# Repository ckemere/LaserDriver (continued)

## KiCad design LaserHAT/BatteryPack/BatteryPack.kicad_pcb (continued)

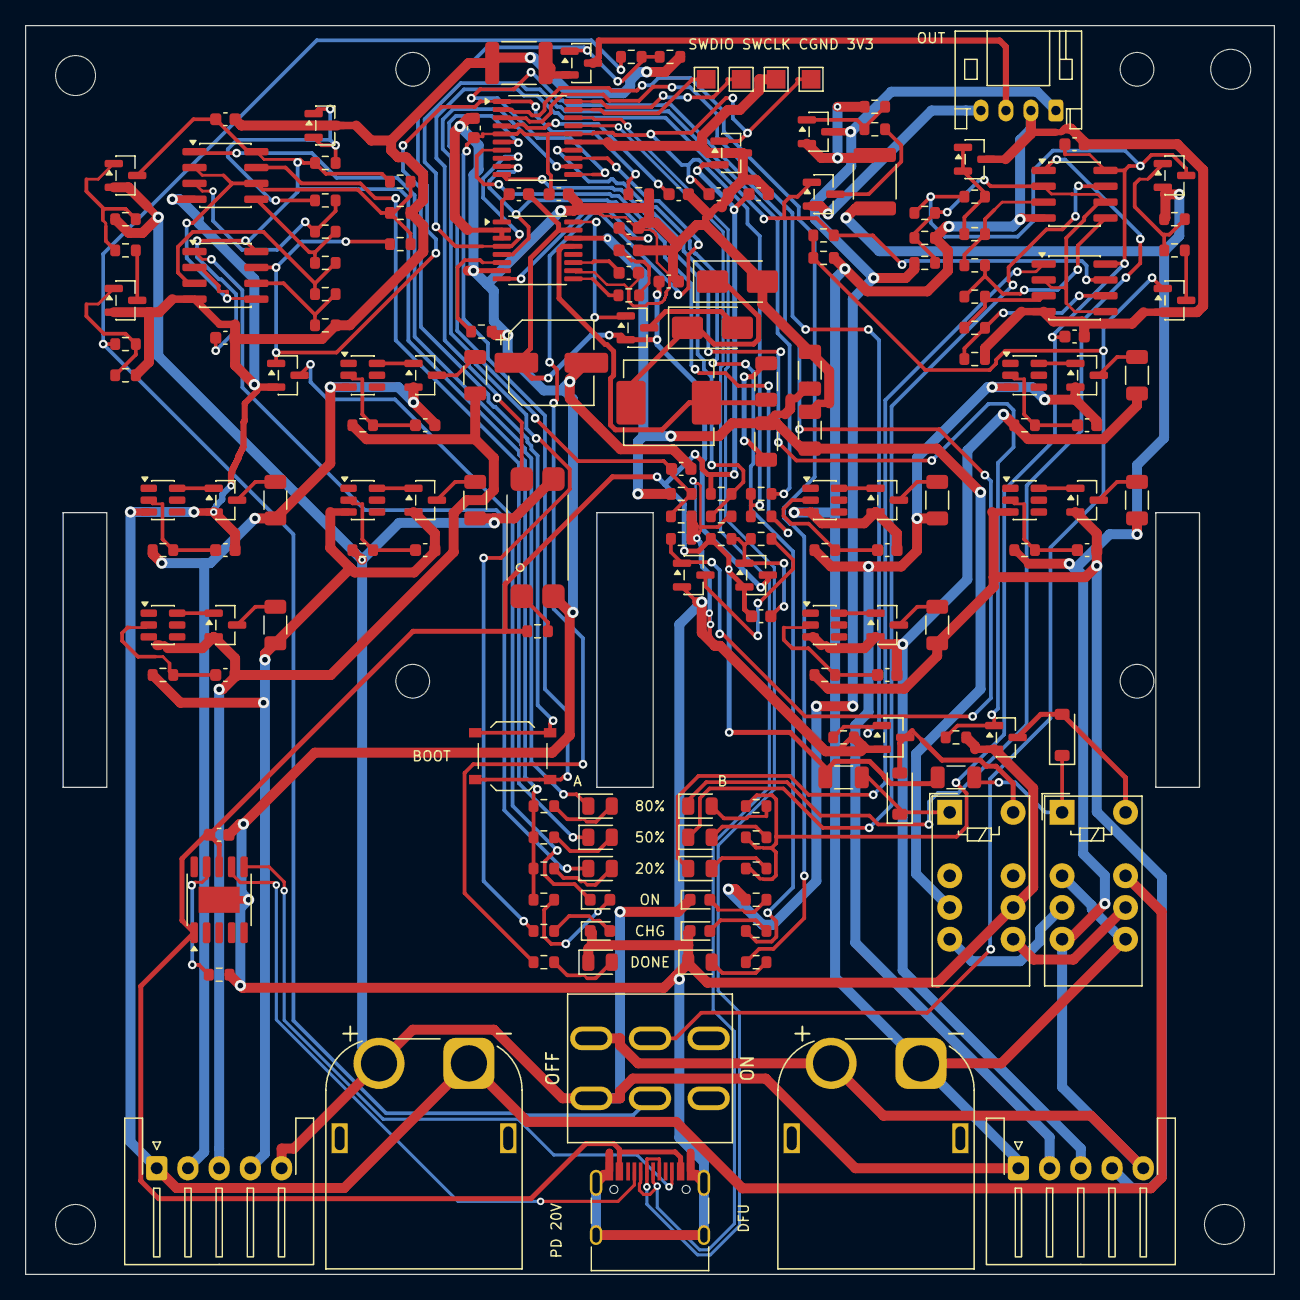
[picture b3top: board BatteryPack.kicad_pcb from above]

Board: 2 copper layers, 100.0 x 100.0 mm, 187 parts (0 on the bottom side), 127 nets.

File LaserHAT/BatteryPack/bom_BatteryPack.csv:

Ref,Value,Footprint,LCSC,Note
J5,S5B-XH-A-1(LF)(SN),JST_XH_S5B-XH-A-1_1x05_P2.50mm_Horizontal,C163038,
J6,S5B-XH-A-1(LF)(SN),JST_XH_S5B-XH-A-1_1x05_P2.50mm_Horizontal,C163038,
J7,XT60PW-M,XT60PW-M,C98732,
J8,XT60PW-M,XT60PW-M,C98732,
SW1,CAX-MTS202B2-BB-20.5JL,SW_MTS-202,C55159891,
R82,1M,R_0603_1608Metric,C22935,
F1,MF-MSMF010-2,Fuse_1812_4532Metric,C12430,
Q1,AO3401A,SOT-23,C15127,
R1,100k,R_0603_1608Metric,C25803,
R2,100k,R_0603_1608Metric,C25803,
Q22,2N7002,SOT-23,C8545,
R81,1M,R_0603_1608Metric,C22935,
U15,LM393DR2G,SOIC-8_3.9x4.9mm_P1.27mm,C7955,
D11,KT-0603R,LED_0603_1608Metric,C2286,
R54,13k,R_0603_1608Metric,C22797,
F2,MF-MSMF010-2,Fuse_1812_4532Metric,C12430,
Q11,AO3400A,SOT-23,C20917,
R39,100k,R_0603_1608Metric,C25803,
R40,100k,R_0603_1608Metric,C25803,
U2,LM393DR2G,SOIC-8_3.9x4.9mm_P1.27mm,C7955,
D1,KT-0603R,LED_0603_1608Metric,C2286,
R12,13k,R_0603_1608Metric,C22797,
Q14,AO3400A,SOT-23,C20917,
Q20,AO3401A,SOT-23,C15127,
R77,100k,R_0603_1608Metric,C25803,
R78,100k,R_0603_1608Metric,C25803,
Q21,2N7002,SOT-23,C8545,
R79,100k,R_0603_1608Metric,C25803,
R80,100k,R_0603_1608Metric,C25803,
Q23,AO3401A,SOT-23,C15127,
R83,100k,R_0603_1608Metric,C25803,
R84,100k,R_0603_1608Metric,C25803,
Q24,2N7002,SOT-23,C8545,
U17,EL817S1(C)(TU)-F,EL817S1,C2912100,
R76,10k,R_0603_1608Metric,C25804,
J1,TYPE-C-31-M-12,USB_C_Receptacle_HRO_TYPE-C-31-M-12,C165948,
U4,CH224A,SSOP-10-1EP_3.9x4.9mm_P1mm_EP2.1x3.3mm,C42459160,
C3,1u,C_0603_1608Metric,C15849,
R24,120k,R_0603_1608Metric,C25808,
U18,TLV76033DBZR,SOT-23,C2683368,
C22,1u,C_0603_1608Metric,C15849,
C23,1u,C_0603_1608Metric,C15849,
Q13,AO3401A,SOT-23,C15127,
R43,100k,R_0603_1608Metric,C25803,
R44,100k,R_0603_1608Metric,C25803,
C28,10n,C_0603_1608Metric,C57112,
Q12,2N7002,SOT-23,C8545,
R42,100k,R_0603_1608Metric,C25803,
U5,CN3704,TSSOP-16_4.4x5mm_P0.65mm,C51659,
C4,100n,C_0603_1608Metric,C14663,
C5,22u 50V,CP_Elec_6.3x5.4,C2836438,
C6,1u,C_0603_1608Metric,C15849,
Q6,AO3401A,SOT-23,C15127,
D7,SS34,D_SMA,C8678,
D8,SS34,D_SMA,C8678,
L1,MWSA0603S-330MT,L_Sunlord_MWSA0603S,C408454,
R25,0.1R,R_1206_3216Metric,C25334,
R26,0.1R,R_1206_3216Metric,C25334,
C7,22u,C_1206_3216Metric,C12891,
C8,22u,C_1206_3216Metric,C12891,
RT1,NCP18XH103F03RB,R_0603_1608Metric,C13564,
C9,470p,C_0603_1608Metric,C1620,
R27,120,R_0603_1608Metric,C22787,
C10,220n,C_0603_1608Metric,C21120,
C11,100n,C_0603_1608Metric,C14663,
R28,10k,R_0603_1608Metric,C25804,
R29,10k,R_0603_1608Metric,C25804,
K1,G6S-2 DC12,Relay_DPDT_Omron_G6S-2,C1525289,
R86,680,R_1206_3216Metric,C17975,
Q19,2N7002,SOT-23,C8545,
R85,100k,R_0603_1608Metric,C25803,
D19,1N4148W,D_SOD-123,C81598,
K2,G6S-2 DC12,Relay_DPDT_Omron_G6S-2,C1525289,
R88,680,R_1206_3216Metric,C17975,
Q25,2N7002,SOT-23,C8545,
R87,100k,R_0603_1608Metric,C25803,
D20,1N4148W,D_SOD-123,C81598,
U19,STM32F042F4P6,TSSOP-20_4.4x6.5mm_P0.65mm,C81002,
C24,100n,C_0603_1608Metric,C14663,
C25,100n,C_0603_1608Metric,C14663,
C26,100n,C_0603_1608Metric,C14663,
R70,10k,R_0603_1608Metric,C25804,
SW2,TS-1187A-B-A-B,SW_Push_1P1T_XKB_TS-1187A,C318884,
R71,1M,R_0603_1608Metric,C22935,
R72,180k,R_0603_1608Metric,C22827,
C27,100n,C_0603_1608Metric,C14663,
R73,100k,R_0603_1608Metric,C25803,
R74,18k,R_0603_1608Metric,C25810,
D9,KT-0603R,LED_0603_1608Metric,C2286,
D10,KT-0805G,LED_0805_2012Metric,C2297,
D17,KT-0603R,LED_0603_1608Metric,C2286,
D18,KT-0805G,LED_0805_2012Metric,C2297,
R66,1k,R_0603_1608Metric,C21190,
R67,470,R_0603_1608Metric,C23179,
R68,1k,R_0603_1608Metric,C21190,
R69,470,R_0603_1608Metric,C23179,
J3,S4B-PH-K-S(LF)(SN),JST_PH_S4B-PH-K_1x04_P2.00mm_Horizontal,C157926,
H1,M3,MountingHole_3.2mm_M3,,
H2,M3,MountingHole_3.2mm_M3,,
H3,M3,MountingHole_3.2mm_M3,,
H4,M3,MountingHole_3.2mm_M3,,
H5,M2.5,MountingHole_2.7mm_M2.5,,
H6,M2.5,MountingHole_2.7mm_M2.5,,
H7,M2.5,MountingHole_2.7mm_M2.5,,
H8,M2.5,MountingHole_2.7mm_M2.5,,
U3,CJ431,SOT-23,C3113,
R3,6.8k,R_0603_1608Metric,C23212,
R4,6.2k,R_0603_1608Metric,C4260,
R5,2k,R_0603_1608Metric,C22975,
R6,2k,R_0603_1608Metric,C22975,
R7,6.2k,R_0603_1608Metric,C4260,
R8,30k,R_0603_1608Metric,C22984,
R9,68k,R_0603_1608Metric,C23231,
R10,10k,R_0603_1608Metric,C25804,
R11,470k,R_0603_1608Metric,C23178,
U1,LM393DR2G,SOIC-8_3.9x4.9mm_P1.27mm,C7955,
C1,100n,C_0603_1608Metric,C14663,
C2,100n,C_0603_1608Metric,C14663,
D2,KT-0805Y,LED_0805_2012Metric,C2296,
D3,KT-0805G,LED_0805_2012Metric,C2297,
D4,KT-0805G,LED_0805_2012Metric,C2297,
R13,13k,R_0603_1608Metric,C22797,
R14,12k,R_0603_1608Metric,C22790,
R15,12k,R_0603_1608Metric,C22790,
U16,CJ431,SOT-23,C3113,
R45,6.8k,R_0603_1608Metric,C23212,
R46,6.2k,R_0603_1608Metric,C4260,
R47,2k,R_0603_1608Metric,C22975,
R48,2k,R_0603_1608Metric,C22975,
R49,6.2k,R_0603_1608Metric,C4260,
R50,30k,R_0603_1608Metric,C22984,
R51,68k,R_0603_1608Metric,C23231,
R52,10k,R_0603_1608Metric,C25804,
R53,1M,R_0603_1608Metric,C22935,
U14,LM393DR2G,SOIC-8_3.9x4.9mm_P1.27mm,C7955,
C20,100n,C_0603_1608Metric,C14663,
C21,100n,C_0603_1608Metric,C14663,
D12,KT-0805Y,LED_0805_2012Metric,C2296,
D13,KT-0805G,LED_0805_2012Metric,C2297,
D14,KT-0805G,LED_0805_2012Metric,C2297,
R55,13k,R_0603_1608Metric,C22797,
R56,12k,R_0603_1608Metric,C22790,
R57,12k,R_0603_1608Metric,C22790,
U6,HY2213-BB3A,SOT-23-6,C113632,
R31,100,R_0603_1608Metric,C22775,
C12,100n,C_0603_1608Metric,C14663,
Q7,AO3400A,SOT-23,C20917,
R35,100,R_1206_3216Metric,C17901,
U7,HY2213-BB3A,SOT-23-6,C113632,
R32,100,R_0603_1608Metric,C22775,
C13,100n,C_0603_1608Metric,C14663,
Q8,AO3400A,SOT-23,C20917,
R36,100,R_1206_3216Metric,C17901,
U8,HY2213-BB3A,SOT-23-6,C113632,
R33,100,R_0603_1608Metric,C22775,
C14,100n,C_0603_1608Metric,C14663,
Q9,AO3400A,SOT-23,C20917,
R37,100,R_1206_3216Metric,C17901,
U9,HY2213-BB3A,SOT-23-6,C113632,
R34,100,R_0603_1608Metric,C22775,
C15,100n,C_0603_1608Metric,C14663,
Q10,AO3400A,SOT-23,C20917,
R38,100,R_1206_3216Metric,C17901,
U10,HY2213-BB3A,SOT-23-6,C113632,
R58,100,R_0603_1608Metric,C22775,
C16,100n,C_0603_1608Metric,C14663,
Q15,AO3400A,SOT-23,C20917,
R62,100,R_1206_3216Metric,C17901,
U11,HY2213-BB3A,SOT-23-6,C113632,
R59,100,R_0603_1608Metric,C22775,
C17,100n,C_0603_1608Metric,C14663,
Q16,AO3400A,SOT-23,C20917,
R63,100,R_1206_3216Metric,C17901,
U12,HY2213-BB3A,SOT-23-6,C113632,
R60,100,R_0603_1608Metric,C22775,
C18,100n,C_0603_1608Metric,C14663,
Q17,AO3400A,SOT-23,C20917,
R64,100,R_1206_3216Metric,C17901,
U13,HY2213-BB3A,SOT-23-6,C113632,
R61,100,R_0603_1608Metric,C22775,
C19,100n,C_0603_1608Metric,C14663,
Q18,AO3400A,SOT-23,C20917,
R65,100,R_1206_3216Metric,C17901,

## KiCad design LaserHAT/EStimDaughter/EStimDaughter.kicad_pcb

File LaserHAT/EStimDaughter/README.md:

# E-stim module for LaserHAT Rev 2 (rev M4)

Isolated, charge-balanced, biphasic constant-current stimulator on a plug-in daughter board for the LaserHAT Rev 2
(Raspberry Pi HAT with an MSPM0G3507). It is one of the HAT's two daughter boards; the other is the laser-diode module.
Interface per `LaserHAT/estim_interface/ESTIM_MODULE_SPEC.md` (§7 = the agreed contract). The board is hand-routed (rev M4c).

> Imported into `LaserHAT/EStimDaughter/` from `kbest/estim_module` (kbest commit `9200766`). It was renamed to match `LaserDaughter/`, with the project files and script paths updated. The kbest repo remains the history: `DESIGN_NOTES.md`'s references to `../biphasic_stim` (rev E, the circuit this module derives from) point there.

Status (rev M4, 2026-09-29): schematic complete and verified (ERC 0, netlist = `sch_parts.py`). **The PCB is placed but not routed** — the user routes it by hand (the M3 autorouted board, before the I²C change, is commit `bbd4e76`). Fab files in `../fab/EStimDaughter` are the M3 set and must be regenerated after routing.

**Files**
- `EStimDaughter.kicad_pro`, `.kicad_sch`, `.kicad_pcb`: the design.
- `estim.kicad_sym` + `sym-lib-table`, `estim.pretty/` + `fp-lib-table`: project symbol and footprint libraries, including the DC-DC footprint and its 3D model. Keep them next to the design files.
- `bom_EStimDaughter.csv`: BOM with LCSC part numbers.
- `renders/`: `3d_top.png`, `3d_bottom.png`, `3d_iso.png`, and `3d_top_ps1_dnp.png` (converter not fitted).
- `sim/`: ngspice simulation of the final circuit, with its one vendor model (section 5).

---

## 1. What the module does

```
 HAT side (GND_H)            ║ barrier ║            isolated side (GND_ISO)
                             ║  2 mm   ║
 J8.2 +5V ──────────────► PS1 isolated DC-DC ────► ±15 V ──► LDO → +5V_ISO
                             ║         ║
 J8.5 PWM_A = EN     ──┐     ║         ║        ┌─► ADG1436 dual SPDT: CATH selects +VSET / −VSET, EN selects that or 0 V
 J8.4 PWM_B = CATH   ──┤ U1  ║ ISO7741F║ ───────┤
 J9.3 RELEASE ────────┘ 3+1  ║         ║        ├─► DG419B SHORT switch across E1–E2: closed while RELEASE is low
 J9.4 SDA ────────────┐ U9   ║ ISO1640 ║ ───────┼─► DAC60501 12-bit I²C DAC, internal 2.5 V ref / 2 = 0–1.25 V
 J9.5 SCL ────────────┘      ║  (I²C)  ║        │      └─► OPA2192 B: unity inverter makes −VSET
 J8.3 FAULT_n ◄──────────────╫─────────╫────────┤  LM393 window on the electrode voltage: low = compliance /
                             ║         ║        │  open-electrode fault (also low while the isolated side is unpowered)
                             ║         ║
                             ║         ║  OPA2192 A: floating-load V→I; I = V_IN / 2.49 kΩ → J1 E1 / E2
```

| Parameter | Value |
|---|---|
| Waveform | Cathodic-first biphasic. Both phases come from one set-point, so they're matched by construction. |
| Current | 0–502 µA, 12-bit (0.123 µA/LSB). Intended range 20–250 µA. |
| Phase width / interphase gap | 20–100 µs each, timed by the HAT |
| Compliance | About ±13.5 V from the ±15 V rails. Into the worst-case electrode (15 kΩ, 1.6 nF) that allows about 220 µs at 100 µA but only about 21 µs at 500 µA. High currents with long phases need a lower-impedance electrode. |
| Charge balance | 0.003–0.07 % phase mismatch (simulated). The SHORT switch, under HAT control (RELEASE), resets the electrode between pairs. |
| Electrode (design load) | Tungsten microwire: Rs 5–15 kΩ, Cdl 1.6–3.2 nF, Rct 2 MΩ |
| Isolation | Functional, to break 60 Hz ground loops (not a safety barrier). Separate grounds, with a 2 mm copper-free gap on every layer. Only the DC-DC (PS1) and the digital isolator (U1) cross it. |
| HAT power | +5 V about 0.1–0.2 A (budget 500 mA). +3.3 V only for the isolator's HAT side (a few mA). |

### HAT interface

| HAT pin | MCU | Module signal |
|---|---|---|
| J8.1, J9.1 GND | — | GND_H |
| J8.2 +5V | — | DC-DC input |
| J8.5 PWM_A | PA7 TIMA0_CCP1 | **EN**: current flows while high |
| J8.4 PWM_B | PA12 TIMA0_CCP3 | **CATH**: 1 = cathodic, 0 = anodic |
| J8.3 GPIO | PA6 TIMA0_FAULT0 | **FAULT_n**: low = fault (electrode voltage past the compliance window, open electrode) or isolated side not powered (module not ready) |
| J9.2 +3V3 | MSPM0_3V3 | ISO7741F / ISO1640 VCC1 |
| J9.3 "DAC" | PA15 as GPIO | **RELEASE**: high = SHORT switch open (electrode free), low = E1 shorted to E2 |
| J9.4 "ADC_A" | PA17 as GPIO (open-drain) | **SDA** (bit-banged I²C) |
| J9.5 "ADC_B" | PA22 as GPIO (open-drain) | **SCL** |

MCU pins per `../REV2_NOTES.md`; the J8/J9 pad positions are frozen, the J9.3–5 meanings changed in rev M4 (`../estim_interface/ESTIM_MODULE_SPEC.md` §7; M1–M3 carried CS_n / SCK / MOSI for an SPI DAC; SDA and SCL swapped places on 2026-09-29 for the layout; J8.3 and J8.5 swapped the same evening so FAULT_n meets the ISO7741's reverse channel — a HAT copper change).

### Firmware contract
- **Amplitude.** Bit-banged I²C (any clock up to 400 kHz; both lines open-drain with 4.7 k pull-ups on both sides of the isolator) to the DAC60501Z at address **0x48**, between trains. After the isolated side powers up (250 µs POR): write the GAIN register **0x04 = 0x0100** (REF-DIV = 1, BUFF-GAIN = 0 → 0–1.25 V full scale; the power-on default is ×2 gain, which would give 4× the intended current), then per amplitude the DAC register **0x08 = code << 4** (12-bit code left-aligned in 16 bits). Frame: address byte 0x90, command byte, data MSB, data LSB. The Z variant powers up at zero code.
  I = code / 4096 × 1.25 V / 2.49 kΩ (0.123 µA/LSB, 502 µA full scale).
- **Pulse pair.**
  1. RELEASE high ≥ 1 µs before the first EN (opens the SHORT switch).
  2. CATH high before EN rises (≥ 1 µs; the ADG1436 switches in ~150 ns).
  3. EN high for t_pw.
  4. EN low for the gap; CATH falls during the gap.
  5. EN high for t_pw.
  6. EN low; RELEASE low when the electrode should be shorted again (recommended: ~200 µs after the pair, for ≥ 200 µs, then either leave it shorted until the next pair or open it for recording).
- **SHORT** is under HAT control through RELEASE: low = E1 shorted to E2 through the DG419B (15 Ω). RELEASE is pulled low on the module and the isolator is fail-safe low, so an unpowered or unconfigured HAT leaves the electrode shorted. A TIMA0 fault kills EN and CATH in hardware; the fault handler should also drop RELEASE.
- **FAULT_n** reads low until the isolated supply is up (treat that as "not ready"), and pulses low whenever the electrode voltage leaves the compliance window during a pulse (see *Fault detector* below). The HAT latches TIMA0_FAULT0 (forces PWM_A/B low) and clears it between trains; a fault during a train therefore ends the train, and the Pi is told.
- **Fail-safe.** EN, CATH and RELEASE are pulled low before the isolator, and the ISO7741F outputs low when its HAT side is unpowered. So an unconfigured or unpowered HAT gives zero current with the electrode shorted. The I²C lines idle high (pull-ups); the DAC only changes on a complete, addressed write.

### Fault detector (rev M2, simplified in M4b)
U8, a TLV1702 dual comparator running from the ±V rails (36 V, rail-to-rail inputs), compares the electrode-side voltage E1 directly with two taps of a single 10 k / 215 k / 10 k string between +V and −V. Each tap sits 0.043 × (V+ + |V−|) inside its rail: |E1| > 0.915·V for equal packs (13.7 V at ±15 V, 11.0 V at ±12 V, 15.4 V at ±16.8 V); with unequal packs both margins become the average (e.g. 1.10 V each at +16.8 / −9 V), and a missing pack holds the fault on. Both open-collector outputs (wired-OR, sinking to −V) reach the isolator through R26 10 k with D2 clamping FAULT_n to GND_ISO; R19 4.7 k pulls it high. Simulated (`sim/fault.py`, full run): it fires 8–13 µs before the electrode current starts to collapse and stays low for the rest of the over-compliance phase; an open electrode trips it ~1 µs after EN rises; in-compliance trains never come within 3 V of the window. The HAT's TIMA0 fault input is latched and forces EN and CATH low, so a train that hits compliance is cut at the first phase that does; firmware should keep the fault input's glitch filter short (≤ 1 µs) or off, clear the latch only between trains, and report the event to the Pi. Because the same line is the module-ready flag, the start-up behaviour (low until +5V_ISO is up) is unchanged. (M2–M4 used an LM393 at 0/5 V with E1 divided and offset: nine resistors; the ±V-supplied comparator needs five and does not load E1.)

---

## 2. Fab and assembly parameters

| Item | Value |
|---|---|
| Outline | **26.5 × 36.5 mm** rectangle, drawn in **HAT board coordinates**: x 101.0–127.5, y 76.0–112.5 mm. The module extends 12.5 mm past the HAT's south edge (y = 100), over the Pi's USB-C / micro-HDMI edge (HAT NOTICE 12). J8/J9 pads land exactly on the HAT sockets. |
| Layers | **4**: F.Cu parts + signals with GND pours / In1.Cu split ground planes (GND_H \| GND_ISO) / In2.Cu power distribution / B.Cu signals with GND pours. (A 2-layer attempt on 2026-09-29 was abandoned.) |
| Thickness | 1.6 mm |
| Track / clearance | 0.15 mm minimum each (signal 0.2 mm, power 0.3 mm) |
| Vias | 0.5 mm pad / 0.3 mm drill, tented. No blind or buried vias. (Board not yet routed in M4.) |
| Hole-to-hole / copper-to-edge | ≥ 0.25 / ≥ 0.3 mm |
| Plated holes | 1.0 mm (headers and DC-DC) |
| Fiducials / tooling / mounting holes | None |
| Silkscreen | 0.8 mm text. Most reference designators are hidden for lack of room, so assembly goes by the CPL. PS1's pads are labelled 5V / GND / −V / 0V / +V. |
| Surface finish, colour | Not specified |

### Assembly

| Side / type | Parts |
|---|---|
| Top SMT (45) | U1 ISO7741F (SSOP-16), U9 ISO1640 (SOIC-8), U2 TLV76050 (SOT-23), U4 DAC60501Z (VSSOP-10), U5 OPA2192 (VSSOP-8), U6 ADG1436 (LFCSP-16 4 × 4 mm), U7 DG419BDQ (MSOP-8), U8 TLV1702 (VSSOP-8), D2 (SOD-323), 34 passives, plus two bare test pads TP1 ISENSE / TP2 GND_ISO |
| Bottom SMT | **none** (single-sided assembly, JLC Economic tier) |
| Through-hole, hand-soldered | **J8, J9**: male 1×5 0.1" headers on the **underside**, into the HAT sockets. **J1**: 1×2 0.1" right-angle electrode header on the south edge. Its plastic body overhangs the edge by about 2.5 mm and its pins by about 9 mm. |
| **DNP** | **PS1**, the isolated 5 V → ±15 V DC-DC (SIP, pins 1 2 4 5 6 on 0.1", 10 mm tall, top side). Fit one of: RECOM **RB-0515D/HP** (Mouser 919-RB-0515D/HP; verified drop-in), Mornsun A0515S-1WR3, or LCSC C5369388 (YLPTEC). Solder it or use a machined-pin SIP socket. Alternatively leave it empty and wire two battery packs: + → **+V**, centre tap → **0V**, − → **−V** (up to ±18 V; draw about 10 mA per rail). |
| LCSC parts | 29 unique (M1: 25; M2 adds LM393DGKR C34440 and the 12 k / 27 k / 110 k 0402 resistors). Stock checked 2026-09-26 for the M1 set; re-run `tools/lcsc_check.py` before ordering. |

Extended parts:
- ICs: ISO7741FDBQR, ISO1640BDR, TLV76050DBZR, DAC60501ZDGSR, OPA2192IDGKR, ADG1436YCPZ, DG419BDQ, TLV1702AIDGKR.
- Diodes: BAT54WS.
- Resistors: 0.1 % 10.0k and 2.49k (0603); 47 Ω (0402).
- Capacitors: 1 µF 50 V (0603 and 0805), 4.7 µF (0603), 2.2 nF (0402).

**Panelization notes**
- The board is **4 layers** (a 2-layer attempt on 2026-09-29 was abandoned); assembly is **single-sided** since M3 (the 23.5 mm outline of M1/M2 could not be routed single-sided; the SMA-connector study of 2026-09-28 was dropped).
- Copper comes within 0.3 mm of the edge. Prefer tab routing with mouse bites to V-scoring.
- Leave a routed gap (not a V-score) along the south edge, where J1 overhangs. J1 is hand-fitted after depanelizing.
- Put fiducials and tooling holes on the panel rails.

---

## 3. Design decisions

| Decision | Reason |
|---|---|
| Digital-only isolation: bit-banged I²C to an isolated DAC (SPI in M1–M3) | No analog signal crosses the barrier, and the amplitude is exact. I²C needs two lines instead of three, which freed J9.3 for the RELEASE line without changing the connectors. A PWM-filtered set-point was evaluated and rejected: amplitude spread, and offset at low codes. |
| ±VSET from one DAC through an inverter, selected by an ADG1436 dual SPDT on the ±V rails (a 74HC4053 with a −5 V zener rail until M4b) | Both phases derive from the same set-point, which gives 0.003–0.07 % charge balance without trimming |
| Floating-load V→I op-amp (OPA2192, ±15 V) with a 2.49 kΩ 0.1 % sense resistor | Current accuracy is set by one precision resistor. The ±15 V rails give about ±13.5 V compliance for 5–15 kΩ electrodes at up to 500 µA. |
| C16, 1 µF DC block in series with the electrode | Safety: no DC can reach tissue under any single fault (stuck EN, latched op-amp, bad DAC code). The worst case is C16 × V ≈ 15 µC, after which the current stops. Normal pulses cost only about 50 mV of compliance. The trade-off: U5A's DC feedback comes from the SHORT closing between pulses (see open items). |
| 502 µA full scale (R14 = 2.49 kΩ, 1.25 V DAC full scale) | Set by the electrode, not the circuit. I_max ≈ 14.5 V / (Rs + 2.5 kΩ + pw/Cdl): about 180–250 µA at 100 µs and 490–690 µA at 20 µs for microwires. For larger or coated electrodes, lower R14 (1.24 k → 1 mA, 619 Ω → 2 mA full scale); nothing else changes. High current on microwires would need higher rails, which means a different op-amp, switch and converter. |
| DAC60501Z with its internal 2.5 V reference (÷2) | ±0.1 % initial reference accuracy, 5 ppm/°C: better than the M1–M3 TL431 + 0.1 % divider it replaces (5 parts), and it speaks I²C. Powers up at zero code. |
| DG419B analog switch for the SHORT (E1 to E2), driven by the HAT's RELEASE line | One ±15 V part, driven straight from the isolator: the HAT decides when the electrode is shorted (M1–M3 derived it from EN/CATH with a 200 µs RC hold timer). Simulated: electrode charge resets to 0 mV every cycle, and the switch's charge injection doesn't accumulate. |
| ISO7741F (3 forward + 1 reverse, fail-safe low) + ISO1640 (bidirectional I²C) | Seven signals across the barrier in two packages; the ISO7741F's defaults are the safe state (EN, CATH, RELEASE low). |
| FAULT_n from a comparator window on E1 (rev E circuit, restored in M2; ±V-supplied TLV1702 since M4b) | Open-collector, so the same line is also the module-ready flag: R19 is unpowered until the isolated side is up. Trip points track the rails (±0.915 V), so the detector works from ±12 V converters to ±18 V battery packs without a change. |
| PS1 is DNP | Keeps the choice open between the DC-DC and batteries. Batteries avoid the converter's switching common-mode noise, which couples through 20–75 pF of isolation capacitance. The isolator adds only about 2 pF. |
| 4 layers, parts on the top only (M3) | The split ground planes on In1.Cu make the isolated domain routable; the 12.5 mm southward extension (26.5 × 36.5 mm) is what made single-sided assembly possible — M1/M2 needed both sides on 23.5 mm. Isolation itself comes from the copper-free barrier, not the layer count. |
| Right-angle 0.1" electrode header on the south edge | The spec's accessible edges are south and west. The cable exits away from the HAT. |

---

## 4. Open items
- **Fab files:** `../fab/EStimDaughter` (gerbers, drill, JLC BOM and CPL). Check part rotations in JLC's placement preview, especially the DHVQFN (U6) and MSOP parts.
- **Enclosure clearance:** the module overhangs the HAT's south edge by 12.5 mm and J1 overhangs the module's south edge by another ~9 mm, above the Pi's USB-C / HDMI cable plugs.
- **Electrode cable:** keep E1-to-ground capacitance under 500 pF (twisted pair, shield tied to E2) for output-stage stability.
- **U5A DC operating point:** C16 blocks DC, so while the SHORT is open U5A has no DC feedback. Its output drifts at about Vos / (R14 · C16), up to about 10 V/s at the OPA2192's ±25 µV maximum offset. The firmware must therefore close the short (RELEASE low) for ≥ ~200 µs at least every ~0.3 s during a train, e.g. after every pair as recommended above; if the electrode is left open for recording, that is also what resets the amplifier.
- **PS1 availability:** one distributor lists the Mornsun A0515S-1WR3 as NRND/obsolete. The RECOM RB-0515D/HP is the verified alternative.

---

## 5. Simulation (`sim/`)

A self-contained ngspice model of the final circuit, with part names matching the schematic. `sim/spice.py` builds the netlists:
- **U5A/U5B (OPA2192):** TI's PSpice macro-model, `sim/models/OPAx192.lib`. The DAC is an ideal source (M4: 0–1.25 V, R14 2.49 k).
- **U8 (TLV1702):** a behavioural open-collector comparator pair (`COMPOC` in `sim/spice.py`: ideal threshold, 0.5 µs delay) with the R26 / D2 level shift; the LM393 macro-model in `sim/models/` is no longer used.
- **Everything else** is modelled from datasheet values: DAC, ADG1436, DG419 with charge injection, BAT54C hold timer, rails, the ISO7761F input load on FAULT_n, and a Randles-cell electrode. `sim/models/README.md` lists every model.

**Requirements**
- ngspice ≥ 40. It's found on `PATH`, or set `NGSPICE=/path/to/ngspice`.
- Python 3 with `numpy` and `matplotlib`.

`spice.run()` puts ngspice in PSpice-compatible mode itself, by writing a `.spiceinit` with `set ngbehavior=psa` next to each temporary deck. No other setup is needed.

**Running**
```bash
cd sim
python stability.py      # U5A loop gain / phase margin vs cable capacitance and electrode   (~1 min)
python setpoint.py       # current accuracy and cathodic/anodic matching, 20-500 uA        (~1 min)
python compliance.py     # max phase width before saturation vs current, 4 rail/electrode cases (~2-5 min)
python train.py          # 5-pair 1 kHz trains with the real SHORT path vs without          (~2-5 min)
python fault.py          # fault detector: trip points, timing vs saturation, open electrode, false trips (~10 min)
```
Add `--quick` to any script for a few-second smoke test with fewer cases. Each script prints a table and writes
`sim/results/<name>.json` and `<name>.png`. Rails default to ±15 V (`RAIL` in `spice.py`; 16.8 V models two 4S Li-ion packs).
Component values are in `VALUES` in `spice.py`, so change them there.

**Expected results.** These were checked in `--quick` mode when the model was written; the full sweeps haven't been run yet.

| Script | Check | Quick-mode result |
|---|---|---|
| `stability.py` | Phase margin ≥ 45° for cable ≤ 500 pF | 70.7° with no cable, 48.4° with 470 pF (Rs 10 k, Cdl 2.2 n) |
| `setpoint.py` | Error vs ideal, and phase matching | 250 µA: −0.35 % in both phases (op-amp tracking of the Cdl ramp, ≈ 1/(2π·GBW·Cdl·R14)), pair charge mismatch −0.006 % |
| `compliance.py` | Max phase width before saturation, worst electrode | 100 µA: 221 µs. 500 µA: 21.5 µs. |
| `train.py` | Charge left on the electrode each cycle | With SHORT, Vcdl after each cycle is +0.8 mV, +1.5 mV, … This is C16 absorbing the net faradaic charge; it converges over about C16·Rct ≈ 2 s. Without SHORT it ratchets to about −1 V. |
| `fault.py` (full run, 2026-09-29, TLV1702 model) | FAULT_n fires before U5A runs out of headroom, never on an in-compliance train | Trip points ±0.915 V (13.7 V at ±15 V). 250 µA phase-width sweeps: FAULT_n goes low 8–13 µs before the electrode current starts to fall (15 V worst electrode: 61.1 vs 69.3 µs; 12 V: 70.2 vs 79.1; 16.8 V: 109.7 vs 122.3; 18 V: 79.1 vs 89.0), mismatch still < 0.02 % when it fires. Open electrode: low 0.9–1.2 µs after EN at 12–18 V. Trains at 250 µA × 60 µs, 100 µA × 100 µs and 20 µA × 20 µs: FAULT_n stays at 4.95 V, ≥ 3.9 V of window margin. (M2 LM393 version, 2026-09-28: 7–12 µs lead, open electrode 3.8 µs.) |

Not modelled:
- component tolerances (0.1 % resistors, TL431, DAC INL/offset);
- the MCP4921's output buffer near 0 V;
- the isolated converter's ripple and common-mode noise.

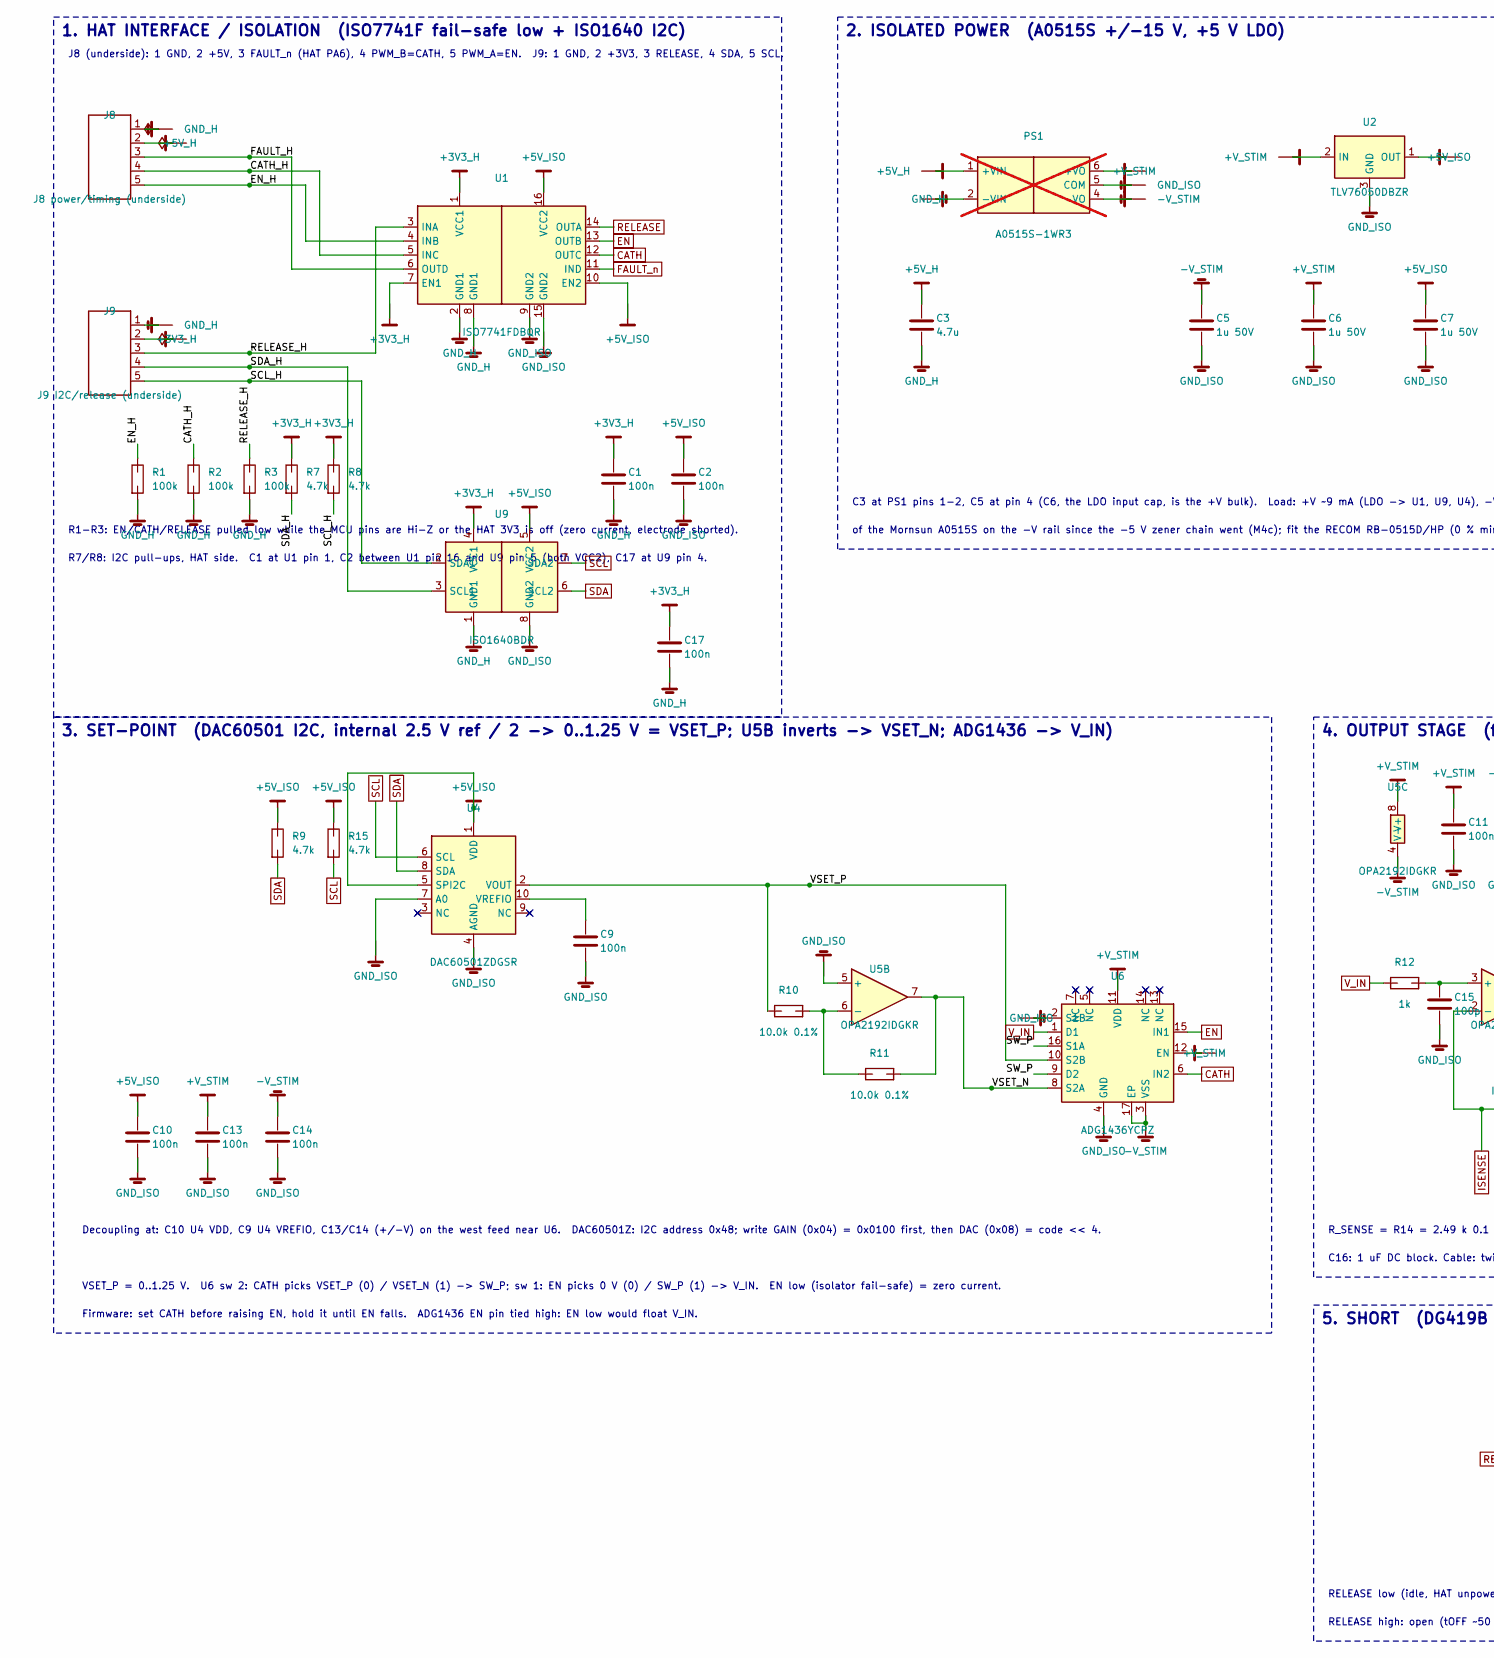
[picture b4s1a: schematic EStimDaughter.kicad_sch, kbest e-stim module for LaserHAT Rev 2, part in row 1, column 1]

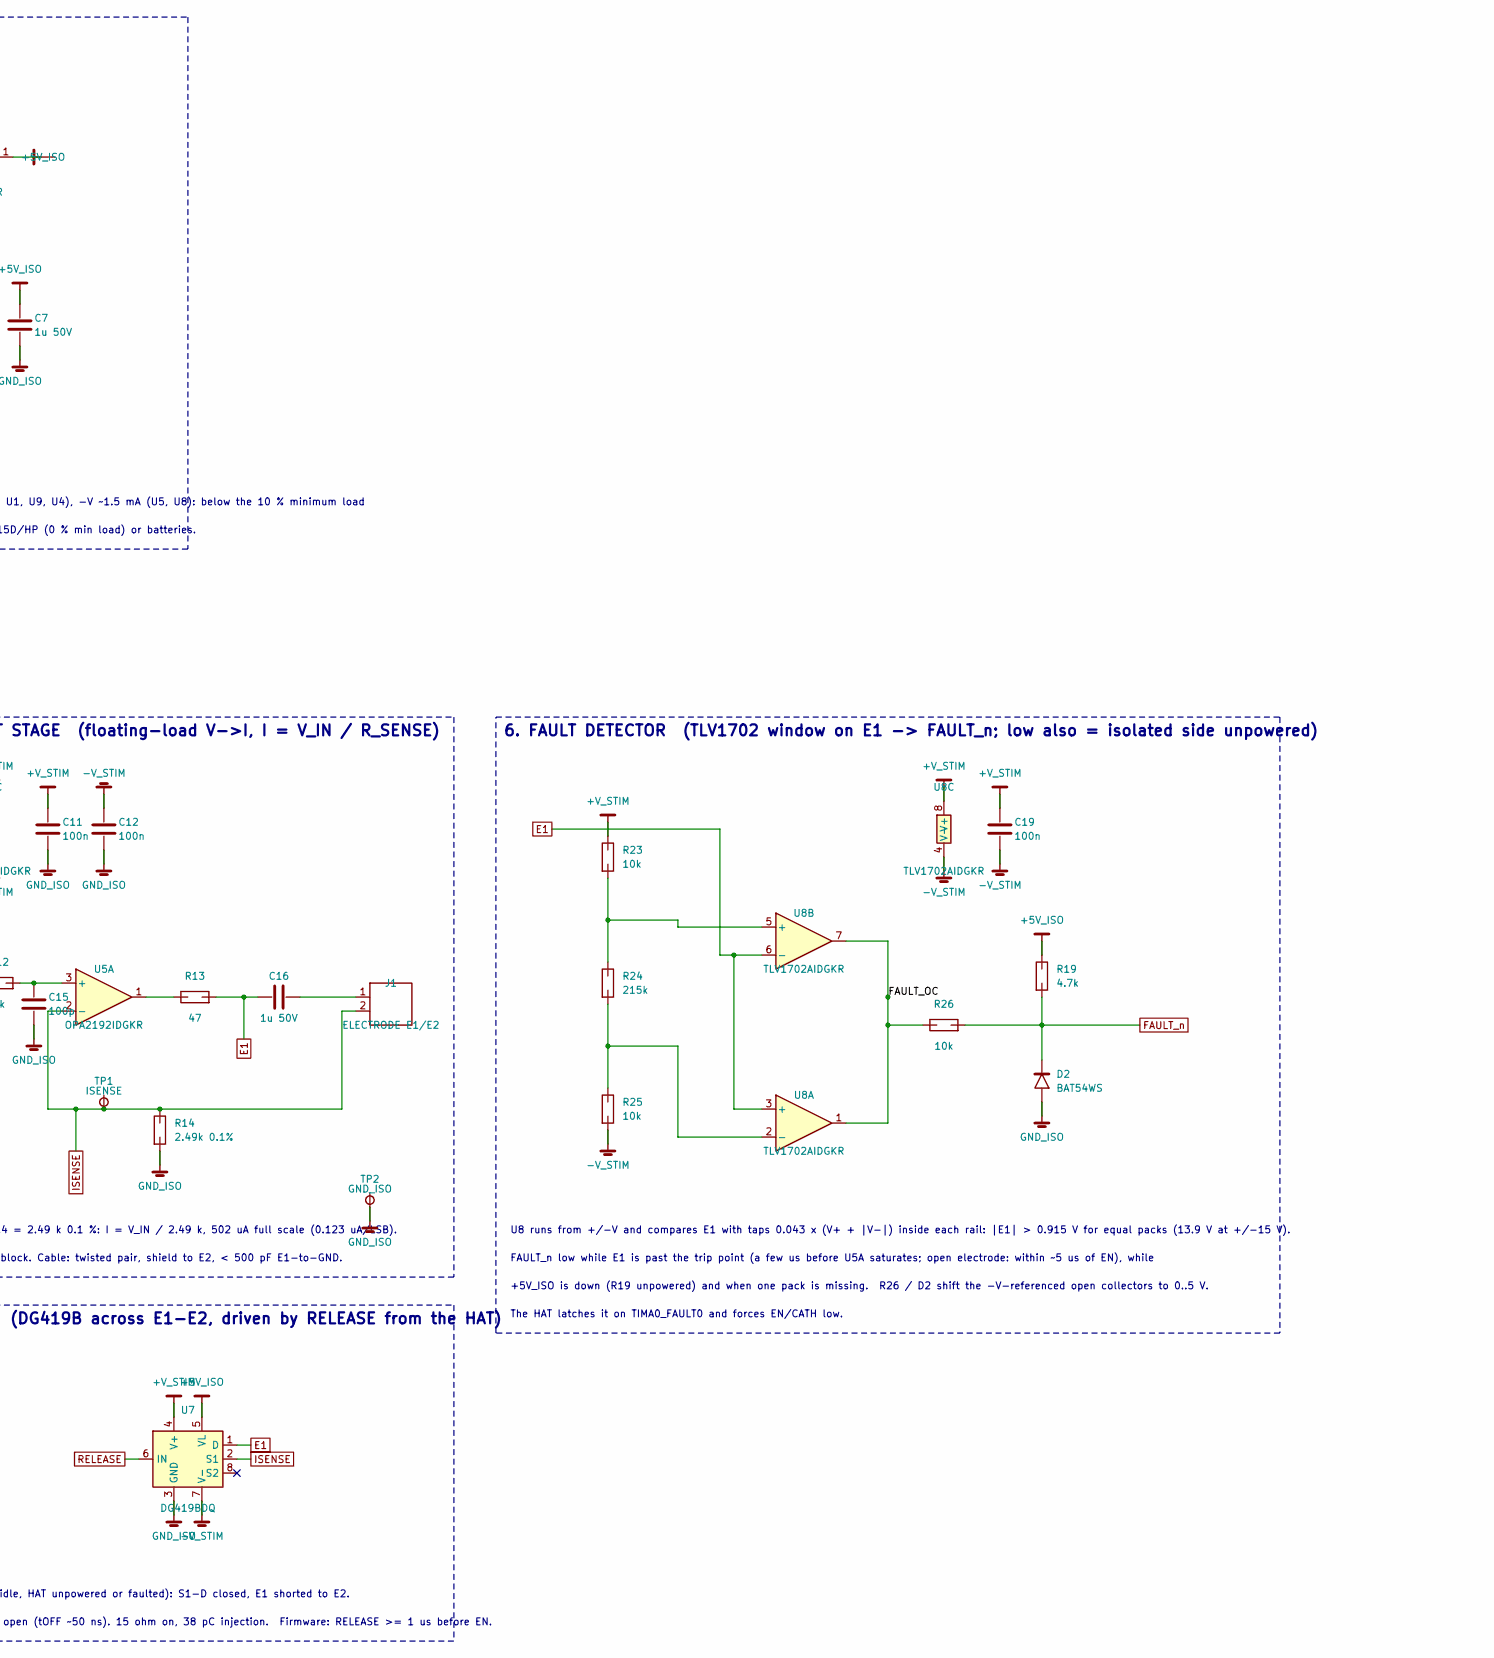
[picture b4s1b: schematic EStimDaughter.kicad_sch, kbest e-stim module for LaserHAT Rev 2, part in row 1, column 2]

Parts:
C1, C2, C9, C10, C17: 100n; C_0402_1005Metric; LCSC C1525
C3: 4.7u; C_0603_1608Metric; LCSC C69335
C5, C6, C7: 1u 50V; C_0603_1608Metric; LCSC C559769
C11, C12, C13, C14, C19: 100n; C_0603_1608Metric; LCSC C14663
C15: 100p; C_0402_1005Metric; LCSC C1546
C16: 1u 50V; C_0805_2012Metric; LCSC C726584
D2: BAT54WS; D_SOD-323; LCSC C124205
J1: ELECTRODE E1/E2; PinHeader_1x02_P2.54mm_Horizontal
J8: J8 power/timing (underside); PinHeader_1x05_P2.54mm_Vertical
J9: J9 I2C/release (underside); PinHeader_1x05_P2.54mm_Vertical
PS1: A0515S-1WR3; DCDC_SIP6_A0515S; not fitted
R1, R2, R3: 100k; R_0402_1005Metric; LCSC C25741
R7, R8, R9, R15, R19: 4.7k; R_0402_1005Metric; LCSC C25900
R10, R11: 10.0k 0.1%; R_0603_1608Metric; LCSC C95204
R12: 1k; R_0402_1005Metric; LCSC C11702
R13: 47; R_0402_1005Metric; LCSC C137973
R14: 2.49k 0.1%; R_0603_1608Metric; LCSC C861299
R23, R25, R26: 10k; R_0402_1005Metric; LCSC C25744
R24: 215k; R_0402_1005Metric; LCSC C185443
TP1: ISENSE; TestPoint_Pad_D1.0mm
TP2: GND_ISO; TestPoint_Pad_D1.0mm
U1: ISO7741FDBQR; SSOP-16_3.9x4.9mm_P0.635mm; LCSC C2872241
U2: TLV76050DBZR; SOT-23; LCSC C2867465
U4: DAC60501ZDGSR; VSSOP-10_3x3mm_P0.5mm; LCSC C1852027
U5: OPA2192IDGKR; VSSOP-8_3x3mm_P0.65mm; LCSC C2876419
U6: ADG1436YCPZ; QFN-16-1EP_4x4mm_P0.65mm_EP2.5x2.5mm; LCSC C655227
U7: DG419BDQ; MSOP-8_3x3mm_P0.65mm; LCSC C2673354
U8: TLV1702AIDGKR; VSSOP-8_3x3mm_P0.65mm; LCSC C2870937
U9: ISO1640BDR; SOIC-8_3.9x4.9mm_P1.27mm; LCSC C5122339

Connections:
+3V3_H: C1.1, C17.1, J9.2, R7.1, R8.1, U1.1 (VCC1), U1.7 (EN1), U9.4 (VCC1)
+5V_H: C3.1, J8.2, PS1.1 (+VIN)
+5V_ISO: C2.1, C7.1, C10.1, R9.1, R15.1, R19.1, U1.10 (EN2), U1.16 (VCC2), U2.1 (OUT), U4.1 (VDD), U4.5 (SPI2C), U7.5 (VL), U9.5 (VCC2)
+V_STIM: C6.1, C11.1, C13.1, C19.1, PS1.6 (+VO), R23.1, U2.2 (IN), U5.8 (V+), U6.11 (VDD), U6.12 (EN), U7.4 (V+), U8.8 (V+)
-V_STIM: C5.2, C12.2, C14.2, C19.2, PS1.4 (-VO), R25.2, U5.4 (V-), U6.3 (VSS), U6.17 (EP), U7.7 (V-), U8.4 (V-)
/CATH_H: J8.4, R2.1, U1.5 (INC)
/EN_H: J8.5, R1.1, U1.4 (INB)
/FAULT_H: J8.3, U1.6 (OUTD)
/FAULT_OC: R26.1, U8.1, U8.7
/RELEASE_H: J9.3, R3.1, U1.3 (INA)
/SCL_H: J9.5, R8.2, U9.2 (SDA1)
/SDA_H: J9.4, R7.2, U9.3 (SCL1)
/SW_P: U6.9 (D2), U6.16 (S1A)
/VSET_N: R11.2, U5.7, U6.8 (S2A)
/VSET_P: R10.1, U4.2 (VOUT), U6.10 (S2B)
CATH: U1.12 (OUTC), U6.6 (IN2)
E1: C16.1, R13.2, U7.1 (D), U8.3 (+), U8.6 (-)
EN: U1.13 (OUTB), U6.15 (IN1)
FAULT_n: D2.1 (K), R19.2, R26.2, U1.11 (IND)
GND_H: C1.2, C3.2, C17.2, J8.1, J9.1, PS1.2 (-VIN), R1.2, R2.2, R3.2, U1.2 (GND1), U1.8 (GND1), U9.1 (GND1)
GND_ISO: C2.2, C5.1, C6.2, C7.2, C9.2, C10.2, C11.2, C12.1, C13.2, C14.1, C15.2, D2.2 (A), PS1.5 (COM), R14.2, TP2.1, U1.9 (GND2), U1.15 (GND2), U2.3 (GND), U4.4 (AGND), U4.7 (A0), U5.5 (+), U6.2 (S1B), U6.4 (GND), U7.3 (GND), U9.8 (GND2)
ISENSE: J1.2, R14.1, TP1.1, U5.2 (-), U7.2 (S1)
unnamed: C16.2, J1.1
unnamed: R13.1, U5.1
unnamed: C9.1, U4.10 (VREFIO)
unnamed: C15.1, R12.2, U5.3 (+)
unnamed: R10.2, R11.1, U5.6 (-)
unnamed: R24.2, R25.1, U8.2 (-)
unnamed: R23.2, R24.1, U8.5 (+)
RELEASE: U1.14 (OUTA), U7.6 (IN)
SCL: R15.2, U4.6 (SCL), U9.7 (SDA2)
SDA: R9.2, U4.8 (SDA), U9.6 (SCL2)
V_IN: R12.1, U6.1 (D1)

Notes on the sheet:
1. HAT INTERFACE / ISOLATION (ISO7741F fail-safe low + ISO1640 I2C)
R1-R3: EN/CATH/RELEASE pulled low while the MCU pins are Hi-Z or the HAT 3V3 is off (zero current, electrode shorted).
R7/R8: I2C pull-ups, HAT side. C1 at U1 pin 1, C2 between U1 pin 16 and U9 pin 5 (both VCC2), C17 at U9 pin 4.
J8 (underside): 1 GND, 2 +5V, 3 FAULT_n (HAT PA6), 4 PWM_B=CATH, 5 PWM_A=EN. J9: 1 GND, 2 +3V3, 3 RELEASE, 4 SDA, 5 SCL.
2. ISOLATED POWER (A0515S +/-15 V, +5 V LDO)
C3 at PS1 pins 1-2, C5 at pin 4 (C6, the LDO input cap, is the +V bulk). Load: +V ~9 mA (LDO -> U1, U9, U4), -V ~1.5 mA (U5, U8): below the 10 % minimum load
of the Mornsun A0515S on the -V rail since the -5 V zener chain went (M4c); fit the RECOM RB-0515D/HP (0 % min load) or batteries.
3. SET-POINT (DAC60501 I2C, internal 2.5 V ref / 2 -> 0..1.25 V = VSET_P; U5B inverts -> VSET_N; ADG1436 -> V_IN)
Decoupling at: C10 U4 VDD, C9 U4 VREFIO, C13/C14 (+/-V) on the west feed near U6. DAC60501Z: I2C address 0x48; write GAIN (0x04) = 0x0100 first, then DAC (0x08) = code << 4.
VSET_P = 0..1.25 V. U6 sw 2: CATH picks VSET_P (0) / VSET_N (1) -> SW_P; sw 1: EN picks 0 V (0) / SW_P (1) -> V_IN. EN low (isolator fail-safe) = zero current.
Firmware: set CATH before raising EN, hold it until EN falls. ADG1436 EN pin tied high: EN low would float V_IN.
4. OUTPUT STAGE (floating-load V->I, I = V_IN / R_SENSE)
R_SENSE = R14 = 2.49 k 0.1 %: I = V_IN / 2.49 k, 502 uA full scale (0.123 uA/LSB).
C16: 1 uF DC block. Cable: twisted pair, shield to E2, < 500 pF E1-to-GND.
5. SHORT (DG419B across E1-E2, driven by RELEASE from the HAT)
RELEASE low (idle, HAT unpowered or faulted): S1-D closed, E1 shorted to E2.
RELEASE high: open (tOFF ~50 ns). 15 ohm on, 38 pC injection. Firmware: RELEASE >= 1 us before EN.
6. FAULT DETECTOR (TLV1702 window on E1 -> FAULT_n; low also = isolated side unpowered)
U8 runs from +/-V and compares E1 with taps 0.043 x (V+ + |V-|) inside each rail: |E1| > 0.915 V for equal packs (13.9 V at +/-15 V).
FAULT_n low while E1 is past the trip point (a few us before U5A saturates; open electrode: within ~5 us of EN), while
+5V_ISO is down (R19 unpowered) and when one pack is missing. R26 / D2 shift the -V-referenced open collectors to 0..5 V.
The HAT latches it on TIMA0_FAULT0 and forces EN/CATH low.

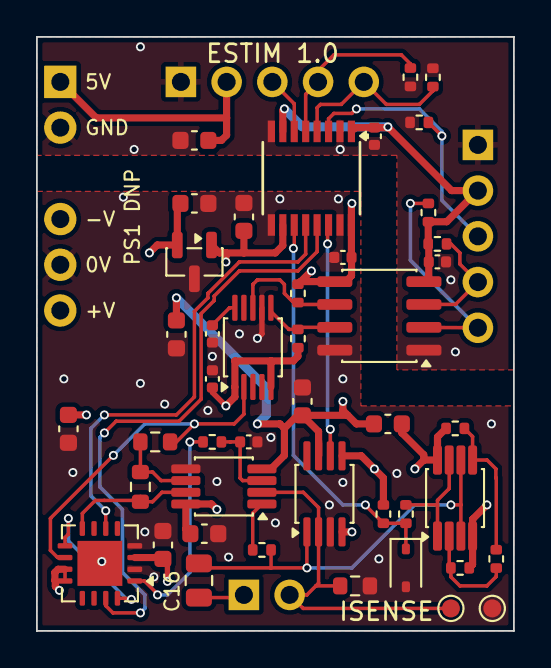
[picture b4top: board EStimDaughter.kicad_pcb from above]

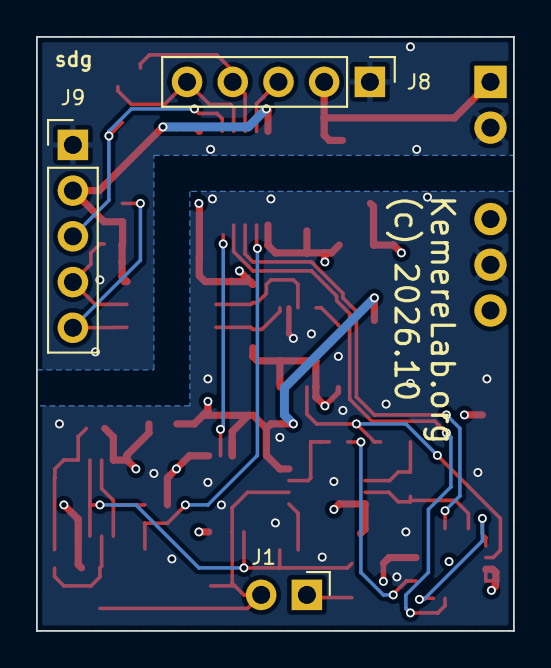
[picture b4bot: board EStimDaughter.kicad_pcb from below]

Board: 4 copper layers, 26.5 x 33.0 mm, 48 parts (3 on the bottom side), 33 nets.

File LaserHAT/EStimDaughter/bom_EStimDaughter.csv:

Ref,Value,Footprint,LCSC,Note
J8,J8 power/timing (underside),PinHeader_1x05_P2.54mm_Vertical,,
J9,J9 I2C/release (underside),PinHeader_1x05_P2.54mm_Vertical,,
R1,100k,R_0402_1005Metric,C25741,
R2,100k,R_0402_1005Metric,C25741,
R3,100k,R_0402_1005Metric,C25741,
R7,4.7k,R_0402_1005Metric,C25900,
R8,4.7k,R_0402_1005Metric,C25900,
U1,ISO7741FDBQR,SSOP-16_3.9x4.9mm_P0.635mm,C2872241,
C1,100n,C_0402_1005Metric,C1525,
C2,100n,C_0402_1005Metric,C1525,
U9,ISO1640BDR,SOIC-8_3.9x4.9mm_P1.27mm,C5122339,
C17,100n,C_0402_1005Metric,C1525,
R9,4.7k,R_0402_1005Metric,C25900,
R15,4.7k,R_0402_1005Metric,C25900,
C3,4.7u,C_0603_1608Metric,C69335,
C5,1u 50V,C_0603_1608Metric,C559769,
U2,TLV76050DBZR,SOT-23,C2867465,
C6,1u 50V,C_0603_1608Metric,C559769,
C7,1u 50V,C_0603_1608Metric,C559769,
U4,DAC60501ZDGSR,VSSOP-10_3x3mm_P0.5mm,C1852027,
C9,100n,C_0402_1005Metric,C1525,
C10,100n,C_0402_1005Metric,C1525,
U5,OPA2192IDGKR,VSSOP-8_3x3mm_P0.65mm,C2876419,
C11,100n,C_0603_1608Metric,C14663,
C12,100n,C_0603_1608Metric,C14663,
R10,10.0k 0.1%,R_0603_1608Metric,C95204,
R11,10.0k 0.1%,R_0603_1608Metric,C95204,
U6,ADG1436YCPZ,QFN-16-1EP_4x4mm_P0.65mm_EP2.5x2.5mm,C655227,
C13,100n,C_0603_1608Metric,C14663,
C14,100n,C_0603_1608Metric,C14663,
R12,1k,R_0402_1005Metric,C11702,
C15,100p,C_0402_1005Metric,C1546,
R13,47,R_0402_1005Metric,C137973,
R14,2.49k 0.1%,R_0603_1608Metric,C861299,
C16,1u 50V,C_0805_2012Metric,C726584,
J1,ELECTRODE E1/E2,PinHeader_1x02_P2.54mm_Horizontal,,
U7,DG419BDQ,MSOP-8_3x3mm_P0.65mm,C2673354,
R19,4.7k,R_0402_1005Metric,C25900,
R23,10k,R_0402_1005Metric,C25744,
R24,215k,R_0402_1005Metric,C185443,
R25,10k,R_0402_1005Metric,C25744,
U8,TLV1702AIDGKR,VSSOP-8_3x3mm_P0.65mm,C2870937,
R26,10k,R_0402_1005Metric,C25744,
D2,BAT54WS,D_SOD-323,C124205,
C19,100n,C_0603_1608Metric,C14663,
